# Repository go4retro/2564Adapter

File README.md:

# 2564Adapter
TMS2564 to JEDEC 27XX(X) Adapter

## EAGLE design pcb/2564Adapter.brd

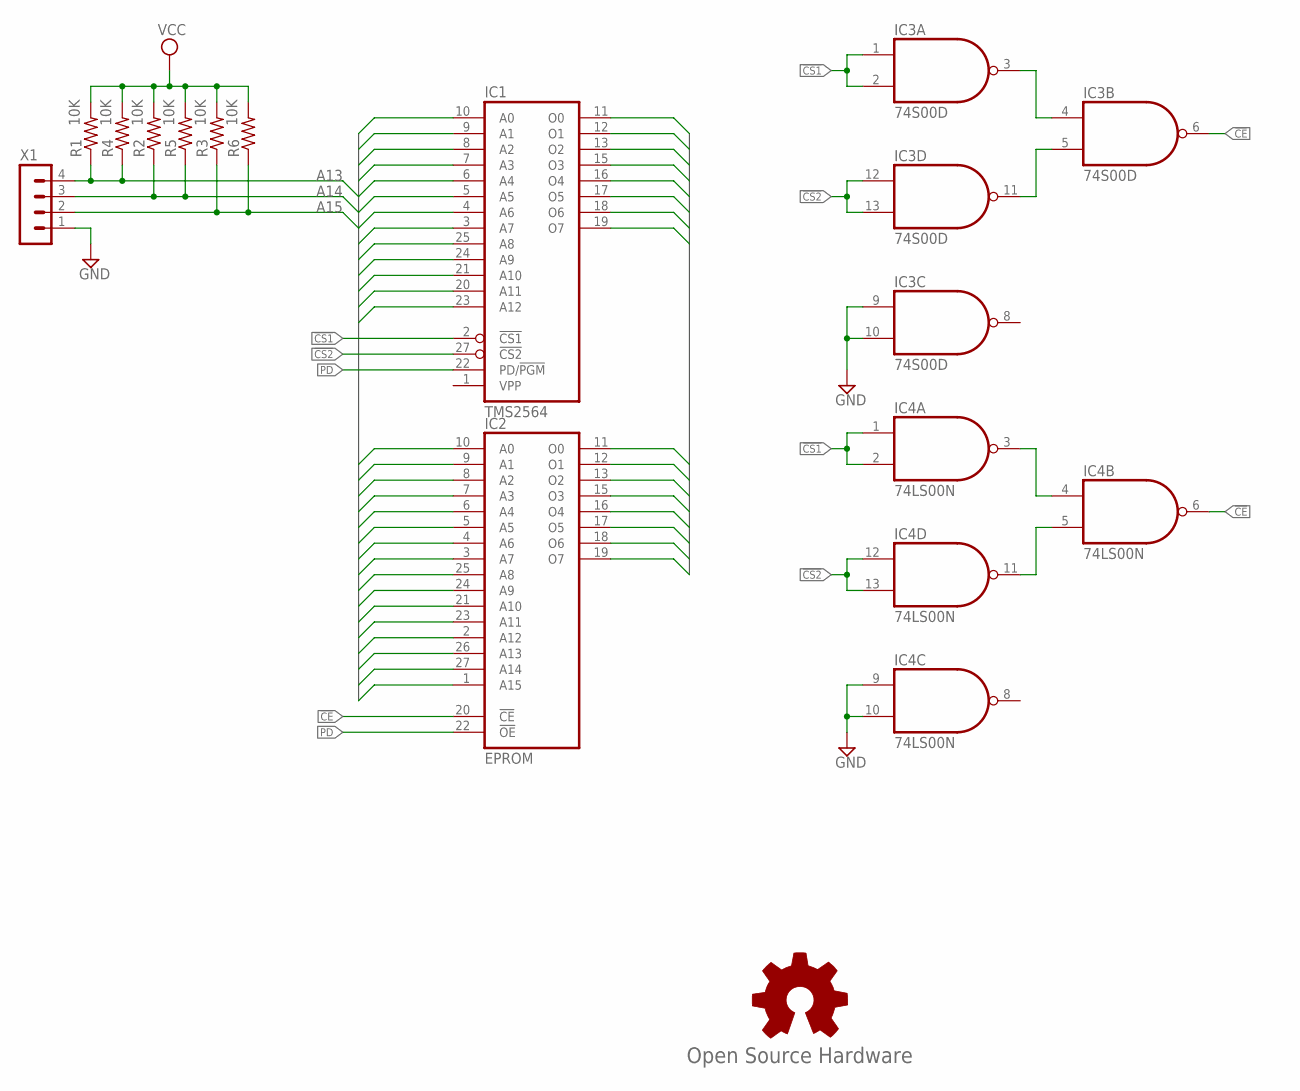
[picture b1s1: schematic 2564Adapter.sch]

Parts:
GOLD_ORB_SM1: Open Source Hardware; OSHW_5MM
IC1: TMS2564; DIL28-ROUNDPAD
IC2: EPROM; DIL28-ROUNDPAD
IC3: 74S00D; SO14
IC4: 74LS00N; DIL14-RP
R1, R2, R3: 10K; 0204/5
R4, R5, R6: 10K; R0805
X1: MA04-1

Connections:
!CE: IC2.20 (!CE), IC3.6 (O), IC4.6 (O)
!CS1: IC1.2 (!CS1), IC3.1 (I0), IC3.2 (I1), IC4.1 (I0), IC4.2 (I1)
!CS2: IC1.27 (!CS2), IC3.12 (I0), IC3.13 (I1), IC4.12 (I0), IC4.13 (I1)
A0: IC1.10 (A0), IC2.10 (A0)
A1: IC1.9 (A1), IC2.9 (A1)
A2: IC1.8 (A2), IC2.8 (A2)
A3: IC1.7 (A3), IC2.7 (A3)
A4: IC1.6 (A4), IC2.6 (A4)
A5: IC1.5 (A5), IC2.5 (A5)
A6: IC1.4 (A6), IC2.4 (A6)
A7: IC1.3 (A7), IC2.3 (A7)
A8: IC1.25 (A8), IC2.25 (A8)
A9: IC1.24 (A9), IC2.24 (A9)
A10: IC1.21 (A10), IC2.21 (A10)
A11: IC1.20 (A11), IC2.23 (A11)
A12: IC1.23 (A12), IC2.2 (A12)
A13: IC2.26 (A13), R1.1, R4.1, X1.4
A14: IC2.27 (A14), R2.1, R5.1, X1.3
A15: IC2.1 (A15), R3.1, R6.1, X1.2
D0: IC1.11 (O0), IC2.11 (O0)
D1: IC1.12 (O1), IC2.12 (O1)
D2: IC1.13 (O2), IC2.13 (O2)
D3: IC1.15 (O3), IC2.15 (O3)
D4: IC1.16 (O4), IC2.16 (O4)
D5: IC1.17 (O5), IC2.17 (O5)
D6: IC1.18 (O6), IC2.18 (O6)
D7: IC1.19 (O7), IC2.19 (O7)
GND: IC1.14 (GND), IC2.14 (GND), IC3.7 (GND), IC3.9 (I0), IC3.10 (I1), IC4.7 (GND), IC4.9 (I0), IC4.10 (I1), X1.1
unnamed: IC4.3 (O), IC4.4 (I0)
unnamed: IC4.5 (I1), IC4.11 (O)
unnamed: IC3.3 (O), IC3.4 (I0)
unnamed: IC3.5 (I1), IC3.11 (O)
PD: IC1.22 (PD/!PGM), IC2.22 (!OE)
VCC: IC1.26 (VCC), IC1.28 (VCC), IC2.28 (VCC), IC3.14 (VCC), IC4.14 (VCC), R1.2, R2.2, R3.2, R4.2, R5.2, R6.2

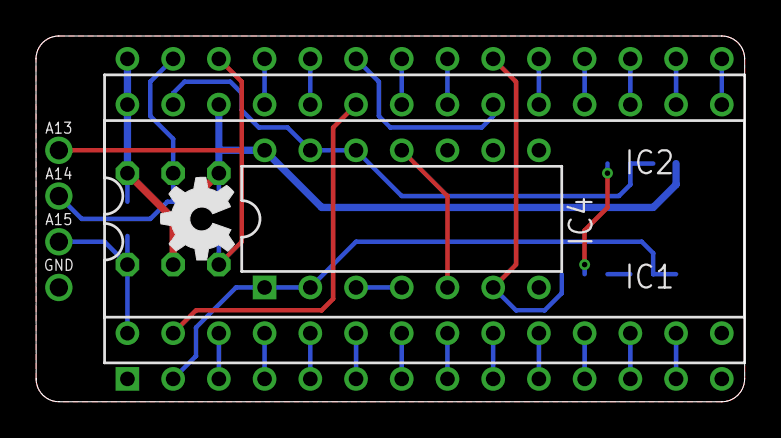
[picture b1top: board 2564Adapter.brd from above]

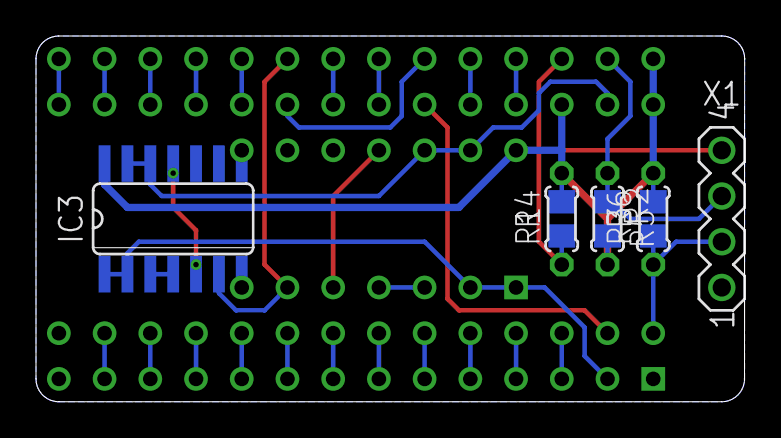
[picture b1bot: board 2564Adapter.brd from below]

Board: 2 copper layers, 39.4 x 20.3 mm, 12 parts (8 on the bottom side), 34 nets.

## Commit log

2018-03-11 Updated license
2018-03-11 Added README.md
2020-01-07 !PGM/PD is a possible select pin, so add in required logic to handle correctly for all cases.
2020-04-14 Added in dimensions
2020-04-24 Add Gerber files
2020-10-11 PCB Updates and BOM cleanup

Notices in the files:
pcb/2564Adapter.brd:
(c) 2018-19 RETRO Innovations
